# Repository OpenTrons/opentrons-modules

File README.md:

# Opentrons Modules

This repository contains:
1. Firmware for all Opentrons modules - Temperature Module (Tempdeck),
Magnetic Module (Magdeck) and Thermocycler.
2. Libraries required to build any module firmware
3. Module board file definitions for Arduino (for the arduino-based modules)
4. Other files required for development & testing

## setup

This repo uses [CMake](https://cmake.org) as a configuration and build management tool. It requires
CMake 3.20 since it uses [presets](https://cmake.org/cmake/help/latest/manual/cmake-presets.7.html)
to manage cross-compilation and project configuration options. 
- Before you can configure any of the cmake presets, you may need to manually install a C compiler and a C++ compiler (e.g. `sudo apt install gcc g++` on Ubuntu)
- If you want to interact with the STM32 hardware, you should also install [st-link](https://github.com/stlink-org/stlink). 

First, clone the repository and change into the directory:

```
git clone git@github.com:Opentrons/opentrons-modules.git
cd opentrons-modules
```

Then,
- If you want to build the arduino modules, run `cmake --preset=arduino .` to set your build step up to build the Arduino-based modules (Magnetic Module, Temperature Module, Thermocycler). This should download the Arduino IDE to the git-ignored `arduino_ide` directory in the repo's working tree. It will also set up a build system in `./builds`.
- If you want to build the STM32 modules, run `cmake --preset=stm32-cross .` to set your build step up to cross-compile the module firmwares for actually putting on modules. This should download the arm cross builds of gcc 10-2020q4 to the git-ignored `stm32-tools` directory in the repo's working tree and set up a build system in `./build-stm32-cross`. By default, this will be a "MinSizeRel" build type, which generates debug symbols packed into the elf and doesn't use optimizations (which makes debugging a lot easier). You can change the build type by adding `-DCMAKE_BUILD_TYPE=<BUILD_TYPE>` on the command line when generating. Valid build types are `Debug`, `MinSizeRel` (default, size optimizations for release - what CI uses to build), and `RelWithDebInfo` (optimizations + debug info, useful if you're seeing failures in the field that don't happen in `Debug` builds).
  - If you want to enable assertions for debugging, add `-DENABLE_ASSERTIONS=ON` to this command. If you don't specify this option, the `configASSERT` lines in compiled firmware will not do anything.
- If you want to build the STM32 module tests, run `cmake --preset=stm32-host .` to set your build step up to host-compile the module fimrware libs and tests for local running. You'll need to have at least a gcc installed; if you have a clang installed, the build will run some clang checker steps. This will set up a build system in `./build-stm32-host`

Since all these configuration steps use separate build dirs (BINARY_DIRS in cmake parlance) you can in fact run all three of these; it's not exclusive. They should all work on any operating system, but the host builds in particular rely on your system compiler and that will therefore need to be set up, which might be a pain on windows.

## build

Each build dir should have a reasonable `all` target (invokable by running `cmake --build <build-dir>`) and individual targets for each module firmware. For instance, the arduino modules have `<module-name>` set up as individual build targets. 

You always have to specify the build dir to run in with `cmake --build`; that can be run from the root of the repo (e.g. by calling `cmake --build ./build-stm32-cross` or `cmake --build ./build`) or as `.` if you navigate into the right build directory first.

To build a specific target, use the `--target` flag: `cmake --build ./build --target magdeck`.

For the arduino modules, the module name target builds the sketch and copies some supporting files like a python-based uploader and a hex for writing the eeprom into `builds/module-name`. For arduino modules, the special target `zip-all` will build zip files of all module firmwares and support files (e.g. eeprom writing): `cmake --build ./build-arduino --target zip-all`. You can then run `cmake --install ./build` and those zip files will be put in the `dist/` directory; this is used in ci.

For stm32 modules, there are module name targets that build the requisite firmware defined in the cross toolchain and the test toolchain alike. In the cross toolchain, these build runnable firmwares; in the host toolchain, they build everything necessary to run tests, but running the tests is done with `cmake --test`.

## upload

This is not implemented in cmake for the arduino modules. Use the Arduino IDE installed to upload the firmware file:

Open the `/modules/.../<file_name>.ino` file in Arduino, select the appropriate board from _Tools->board_,
 select the correct port from _Tools->Port_. Select Upload or _Sketch->Upload_

* NOTE: For Thermocycler, you can also use the `firmware_uploader.py` script in thermo-cycler/production to upload the binary.

The stm32 modules have debug harnessing built in; for instance, running `cmake --build ./build-stm32-cross --target heater-shaker-debug` will build the firmware and spin up the cross gdb and openocd. This target by default (because of commands in the gdbinit) will reset the board and upload the built firmware; if you want to use the firmware currently flashed to the board, run everything manually.

The stm32 modules also have flash targets for when you want to flash the board but not actually run a debugger; running `cmake --build ./build-stm32-cross --target heater-shaker-flash` will build the firmware and then use openocd to flash it to the target.

## test

This is not implemented for the arduino modules.

For the STM32 modules, if you configure the host toolchain: `cmake --preset=stm32-host .`, you can then run the `build-and-test` target: `cmake --build ./build-stm32-host --target build-and-test`, which will build the tests and then run them. You can also use cmake's built-in `test` target: `cmake --build ./build-stm32-host --target test`, but this will not automatically actually build the tests.

Individual tests may set their own check targets; for instance, you can build and run only the heater-shaker tests by running `cmake --build ./build-stm32-host --target heater-shaker-build-and-test`.

If you are on OSX, you almost certainly want to force cmake to select gcc as the compiler used for building tests, because the version of clang built into osx is weird. We don't really want to always specify the compiler to use in tests, so forcing gcc is a separate cmake config preset, and it requires installing gcc 10:

`brew install gcc@10`
`cmake --preset=stm32-host-gcc10 .`

You should specifically do this if you're seeing errors about `concepts` not existing, or `forward_iterator` not existing, or the like.

You can change to a different compiler, like an installed upstream clang/llvm, by changing the cache variables `CMAKE_C_COMPILER` and `CMAKE_CXX_COMPILER`, or by making a custom configuration (see below) that specifies them.

This isn't the default `stm32-host` because it requires specifying the compiler by version to actually work on OSX, where `gcc` and `g++` unqualified by version are... aliased to system clang. Setting the default to `gcc-10` and `g++-10` then might have problems on other platforms if someone update their gcc and g++ or on CI.

## code coverage

This repository is configured to generate code coverage from the tests.

To enable code coverage, configure the host toolchain for tests with the options `-DENABLE_COVERAGE=On -DCMAKE_BUILD_TYPE=Debug`. _In order for code coverage to be accurate, you must run the build-and-test target for a module_. After running every build-and-test target, the target `lcov` will generate an HTMl report of the code coverage from the tests.

In general, do not enable code coverage unless you need it. Test execution will be far slower.

### Custom Configuration

CMake allows you to set preset overrides through a gitignored file called CMakeUserPresets.json. An example (that implements `stm32-host-gcc`, which is the preset above, as an example) is bundled in the `examples/` folder. To apply it, you would copy it into the root of the repo after checkout. `CMakeUSerPresets.json` works exactly like `CMakePresets.json`, but lets you make system- or IDE-specific configuration. In general, presets in `CMakeUserPresets` should inherit from those in `CMakePresets`, since most of the settings in the checked-in presets are good and only a couple need to be changed, but really it's up to you.

## Contributing

When writing or changing the cmake build system, please follow [modern CMake](https://cliutils.gitlab.io/modern-cmake) practices. Use targets; use generator expressions to set properties on those targets rather than setting ``CMAKE_DEBUG_FLAGS``; write CMake like the programming language it is.

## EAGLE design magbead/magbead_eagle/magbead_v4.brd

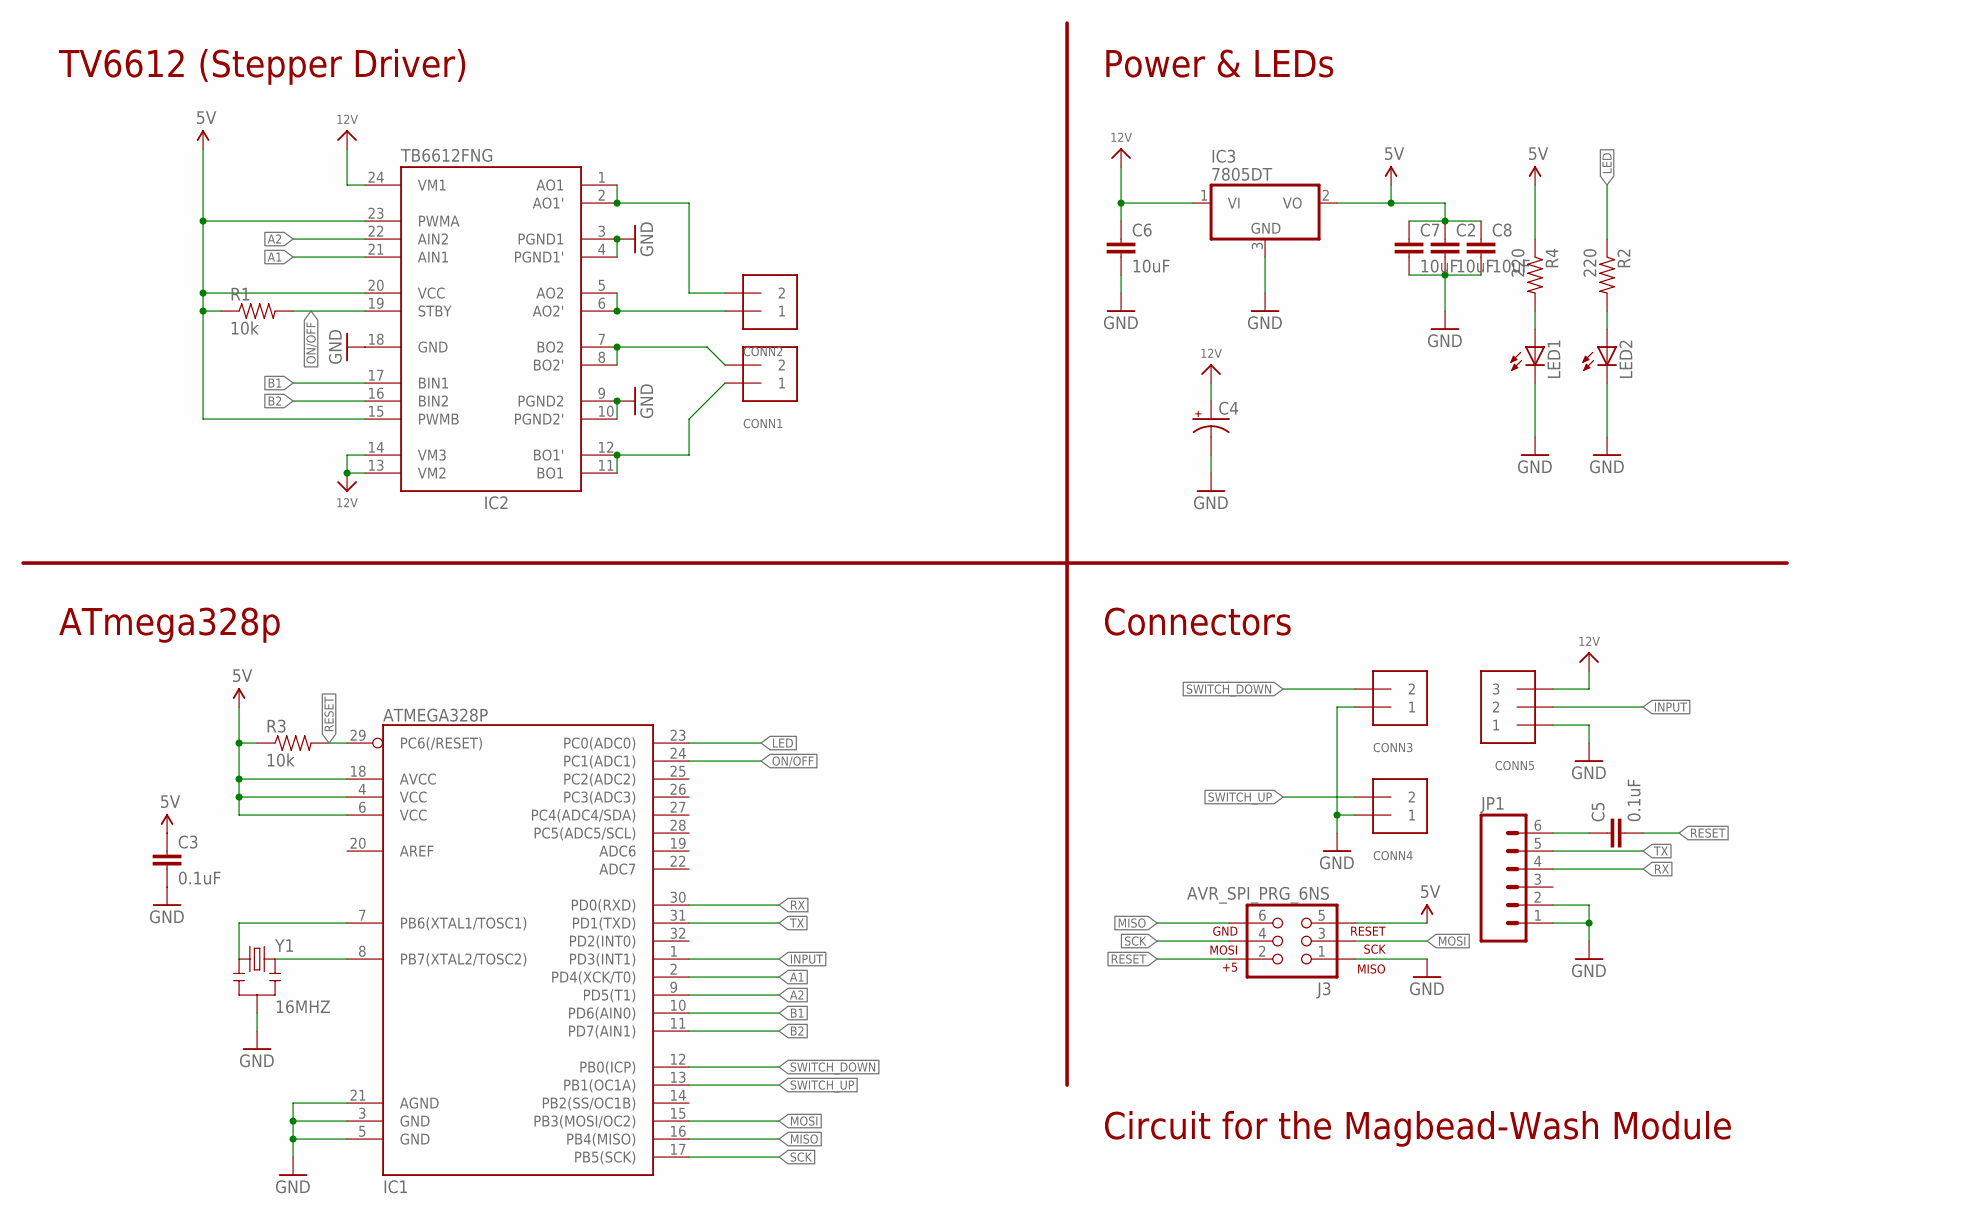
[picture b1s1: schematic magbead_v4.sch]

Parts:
C2, C6, C7, C8: 10uF; 0805
C3, C5: 0.1uF; 0603-CAP
C4: CAP_POLD; PANASONIC_D
CONN1, CONN2, CONN3, CONN4: TERMBLOCK_1X2; TERMBLOCK_1X2-3.5MM
CONN5: TERMBLOCK_1X3; TERMBLOCK_1X3-3.5MM
IC1: ATMEGA328P; TQFP32-08
IC2: TB6612FNG; SSOP24
IC3: 7805DT; TO252
J3: AVR_SPI_PRG_6NS; 2X3-NS
JP1: M06SIP; 1X06
LED1, LED2: LEDCHIP-LED0603; CHIP-LED0603
R1, R3: 10k; 0603-RES
R2, R4: 220; 0603-RES
Y1: 16MHZ; RESONATOR-SMD

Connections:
5V: C2.1, C3.1, C7.1, C8.1, IC1.4 (VCC), IC1.6 (VCC), IC1.18 (AVCC), IC2.15 (PWMB), IC2.20 (VCC), IC2.23 (PWMA), IC3.2 (VO), J3.5, R1.1, R3.1, R4.1
12V: C4.+, C6.1, CONN5.3, IC2.13 (VM2), IC2.14 (VM3), IC2.24 (VM1), IC3.1 (VI)
A1: IC1.2 (PD4(XCK/T0)), IC2.21 (AIN1)
A2: IC1.9 (PD5(T1)), IC2.22 (AIN2)
B1: IC1.10 (PD6(AIN0)), IC2.17 (BIN1)
B2: IC1.11 (PD7(AIN1)), IC2.16 (BIN2)
GND: C2.2, C3.2, C4.-, C6.2, C7.2, C8.2, CONN3.1, CONN4.1, CONN5.1, IC1.3 (GND), IC1.5 (GND), IC1.21 (AGND), IC2.3 (PGND1), IC2.4 (PGND1'), IC2.9 (PGND2), IC2.10 (PGND2'), IC2.18 (GND), IC3.3 (GND), J3.1, JP1.1, JP1.2, LED1.C, LED2.C, Y1.2
INPUT: CONN5.2, IC1.1 (PD3(INT1))
LED: IC1.23 (PC0(ADC0)), R2.1
MISO: IC1.16 (PB4(MISO)), J3.6
MOSI: IC1.15 (PB3(MOSI/OC2)), J3.3
unnamed: LED2.A, R2.2
unnamed: CONN2.2, IC2.1 (AO1), IC2.2 (AO1')
unnamed: LED1.A, R4.2
unnamed: IC1.8 (PB7(XTAL2/TOSC2)), Y1.3
unnamed: IC1.7 (PB6(XTAL1/TOSC1)), Y1.1
unnamed: C5.1, JP1.6
unnamed: CONN2.1, IC2.5 (AO2), IC2.6 (AO2')
unnamed: CONN1.2, IC2.7 (BO2), IC2.8 (BO2')
unnamed: CONN1.1, IC2.11 (BO1), IC2.12 (BO1')
ON/OFF: IC1.24 (PC1(ADC1)), IC2.19 (STBY), R1.2
RESET: C5.2, IC1.29 (PC6(/RESET)), J3.2, R3.2
RX: IC1.30 (PD0(RXD)), JP1.4
SCK: IC1.17 (PB5(SCK)), J3.4
SWITCH_DOWN: CONN3.2, IC1.12 (PB0(ICP))
SWITCH_UP: CONN4.2, IC1.13 (PB1(OC1A))
TX: IC1.31 (PD1(TXD)), JP1.5

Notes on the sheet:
Power & LEDs
Connectors
ATmega328p
TV6612 (Stepper Driver)
Circuit for the Magbead-Wash Module

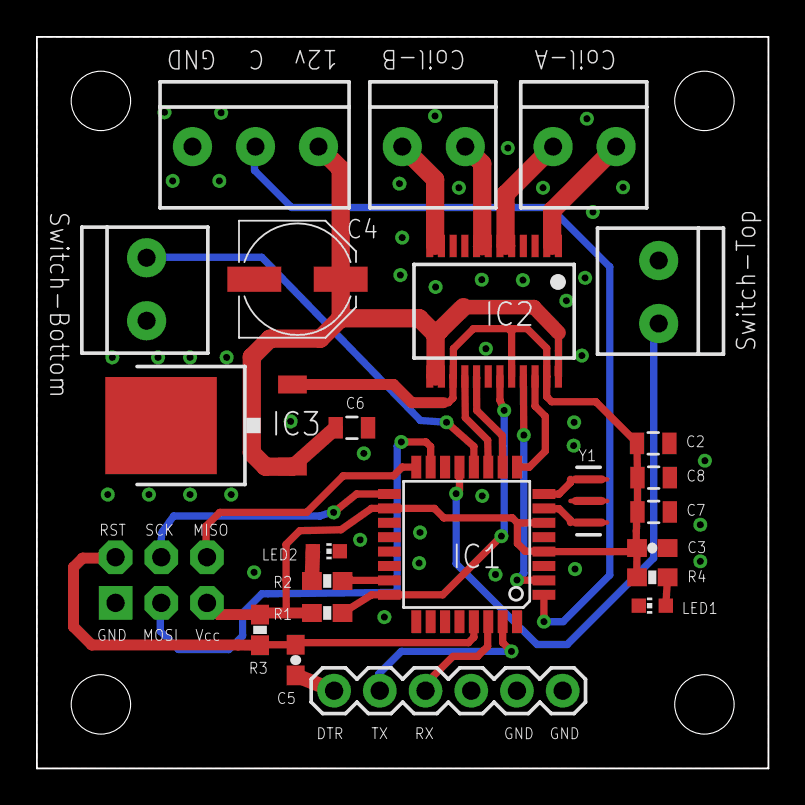
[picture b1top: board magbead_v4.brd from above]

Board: 2 copper layers, 40.6 x 40.6 mm, 24 parts (0 on the bottom side), 27 nets.

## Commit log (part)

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2025-04-03 format
2025-04-04 extra imports
2025-04-14 fix(flex-stacker): ui task fixes and improvements to performance and utility.
2025-04-15 - remove unused freertos timer from motor task - Only enable/disable sensor when there is a state change.
2025-04-23 add task_ready sync status for host comms
2025-04-24 format common
2025-04-24 fix(flex-stacker): Various fixes + improvements for the Flex Stacker UI task and statusbar. (#522)
2025-05-06 always clear cache after error
2025-05-12 fix(thermocycler): clear cache after motor-related errors (#523)
2025-05-12 dont treat error like a flag
2025-05-14 only check limit switch at end of sequence
2025-05-15 update brake delay
2025-05-15 fixup! update default motor currents
2025-05-15 remove semicolon
2025-05-16 remove comment
2025-05-16 fix(flex-stacker): add atomics + remove the UNEXPECTED_LIMIT_SWITCH error from the motor interrupt. (#526)
2025-05-20 test working j gross
2025-05-20 extra whitespace
2025-06-13 Grab reset flags on startup (#485)
2025-06-16 fix print statement
2025-06-16 put default handling in the default case
2025-06-16 gitignore
2025-06-20 cast code to string
2025-06-25 board rev b2 for PVT
2025-08-12 Flex Stacker Release v1.0.0
2025-08-26 fix(flex-stacker): Explicitly enable the limit switch irq on boot to clear any pending irqs held after a fw update.
2025-09-02 add TRAVIS_TAG to get correct arduino module being built
2025-09-02 remove debug
2025-09-15 implement the set_ramp_rate message.
2025-09-15 update tests.
2025-09-16 hetaer-shaker: add test gcodes and basic tests
    Adds M412.D (set error debug), M413 (clear error state), and M411 (get
    error state). These are for checking on and controlling the tracked
    error state of the heater shaker heater and motor tasks for asynchronous
    error generation.
2025-09-16 add clear error state tests
2025-09-16 refactor: clear state motor tests
2025-09-16 fix sim
2025-09-17 reset the leds after power is reset
2025-09-18 refactor: pull some repetitive includes out of tests
2025-09-19 refactor: improve tests
    Take the same approach to the tests as the heater-shaker, condensing
    host comms message checking.
2025-09-19 feat: thermal plate get-error
2025-09-19 feat: add error handling to thermal plate
    The error handling works like this:
    - We will save an "interrupted-by" error that persists until the next
    GetErrorState message, even if the error that caused it originally goes
    away. This is important so that we don't miss transient errors that
    cancelled any ongoing work
    - We get an ongoing error state in preference to an interrupted-by
2025-09-19 Format lots of stuff
2025-09-22 fix: allow messages on subsequent HCT runs
    If the host comms task sends responses too fast it'll clobber the
    previous buffer. Avoid this with a nice little sleep since the stm32 usb
    class doesn't appear to let you see when a buffer has been sent.
2025-09-22 fix lint
    The null pointer thing might be this bug:
    https://bugs.llvm.org/show_bug.cgi?id=46235 the others are just a little
    gross. I might want to disable the constant array index one because if
    you're not going to tolerate exceptions, as we don't, then it's not a
    good idea.
2025-09-24 format said test
2025-09-30 heater-shaker: add a wait after send
    This looks gross and is gross but fixes an issue where if the host comms
    task has two messages to send in quick succession, you can end up
    running again swapping out the tx buffer before it actually hits the wire.
2025-10-01 add usb tx backpressure
    We can actually get whether the usb is busy out of the usb cdc
    machinery. We can use that to handle delaying and retrying if the usb is
    busy, and waiting until the usb transaction completes to actually send data.
2025-10-01 feat(reference-module): add reference module project (#535)
2025-10-03 feat(vacuum-module): add vacuum module project
2025-10-14 fix(thermocycler-gen2): reset lid pos cache if err
    Our fix to EXEC-1451 was to detect if the lid status switches detected
    that we weren't actually closed after the seal extended and return an
    error. This works great. The problem is that because this check happens
    in the lid state machine, the lid _hinge_ state machine has already done
    its work and cached that the lid is closed. Then, when the robot retries
    the command, the lid switches report in-between but we fall back to the
2025-10-15 feat(vacuum-module): add status bar led support.
2025-10-17 feat(vacuum-module): add support for the IS31FL LED driver and status bar animations and controls. (#539)
2025-10-23 use HAL_I2C_Master_Transmit_IT and HAL_I2C_Master_Receive_IT directly and add hal_i2c_master_read and hal_i2c_master_write respective functions fix an issue with the i2c3 buss init
2025-10-23 feat(reference/vacuum-module): Fix gpio issues with i2c3 + add hal_i2c_master_read and hal_i2c_master_write (#540)
2025-10-29 MPR Pressure Sensor hw setup
2025-10-30 temp
2025-10-30 format again
2025-11-03 add vent/pump hardware and policy
2025-11-04 rm stale comments/code
2025-11-04 save
2025-11-05 turn off pump on start
2025-11-06 rm old code + comment
2025-11-06 move sensor hw init
2025-11-06 include hw files in CMakeList
2025-11-06 handle 16-bit timer overflows for accurate tick count
2025-11-07 add pressure control task
2025-11-07 cstdint
2025-11-07 make read buff global variable
2025-11-07 make 0 retries possible
2025-11-07 use write buffer
2025-11-10 - fixed an issue with timing the abs and atm pressure from both sensors - fixed an issue with converting the pressure readings correctly - fixed an issue with the i2c_master_write was being used inst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
2025-11-12 add pressure_task and pump_task skeletons
2025-11-12 remove i2c dep from pump task
2025-11-12 add get pressure engine task
2025-11-13 remove unused vacuum / atmosphere pressure policy use 0x5D instead of 0x5C for atmospheric sensor, since its pull high add sleep_ms to i2c_comms class instantiate abs/atm pressure sensors and get fir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
2025-11-13 add driving mechanism for pressure get and integration
2025-11-13 read abs sensor b, for testing
2025-11-14 fix write + sleep
2025-11-14 rename MPRL to lowercase
2025-11-14 use resume/suspend to start/stop the get pressure task
2025-11-14 add pump control + pid for pump task
2025-11-15 add GetPumpState gcode
2025-11-15 remove unused pressure dirs
2025-11-17 add pressure readings from all 3 pressure sensors
2025-11-18 save pressure/pump controls
2025-11-20 lint
2025-11-25 gets test data through gcode
2025-11-26 formatting
2025-11-26 make read function returns optional
2025-12-01 pump control changes
2025-12-02 unneeded i2c change
2025-12-02 get good gcode readings
2025-12-03 more adjustments for pump task
2025-12-03 pressure regulation achieved
2025-12-04 add is_device_ready to reference-module
2025-12-05 debugging
2025-12-10 save changes for optimizing the pressure task
2025-12-12 after rebase
2025-12-16 - fix timerwrap underflow bug - fix blind start when not enough samples - fix rpm read latensy by decreasing rpm filter alpha
2025-12-16 add EMA pressure filter
2025-12-19 fix issue with atm pressure sensor for nff2 board, which uses ic lps22hb instead of lps22df
2025-12-28 use target guage pressure instead of absolute pressure for user interface
2026-01-05 fix issue parsing negative pressure values
2026-01-07 add comment to explain how the pressure control works
2026-01-07 filter added to new driver version, not used
2026-01-07 filter convolution version
2026-01-08 feat(vacuum-module): Add the pressure and pump control architecture + base gcodes (#544)
2026-01-12 fixed buffer index bug
2026-01-14 clean up comments,test code
2026-01-14 remove filtering from pressure task
2026-01-15 use std arrays
2026-01-15 actual convolution- works
2026-01-15 lint happy + works
2026-01-15 use size_t for buffers + rm sensor_alpha
2026-01-15 comment
2026-01-15 shorter filter
2026-01-20 feat(vacuum-module): set up FIR filtering for vacuum pressure sensor readings (#547)
2026-01-27 separate sensor read set up, still has compile errors
2026-02-11 call send pressure state from GPIO it
2026-02-18 feat(vacuum-module): add product id for vacuum module.
2026-02-19 feat(vacuum-module): add gcodes to tune the pressure control PID parameters.
2026-02-19 fix(build): add vacuum-module to set_build_vars script to deploy the firmware to aws.
2026-02-24 fix(vacuum-module): convert unweighted filter to EMI when filtering mprll0025pa00001a pressure readings.
2026-02-26 get command issues timestamp
2026-02-26 return after stop vacuum + rm dummy function from atm sensor driver
2026-02-26 add solid state tracking + duration
2026-03-02 software timer working
2026-03-05 vent after working
2026-03-05 rm some old comments
2026-03-06 use send_error_message + rename sstp
2026-03-06 feat(vacuum-module): add a slope monitoring mechanism for waste full detection.
2026-03-06 change SetVentState to use VentState enum instead of bool
2026-03-09 feat(vacuum-module): Expose temperature in Celcius from the lps22hb pressure sensor.
2026-03-11 split out pressure control and waste detection into seperat classes
2026-03-17 feat(vacuum-module): Add a waste full detection mechanism using pressure slope monitoring (#555)
2026-03-18 feat(vacuum-module): add SetWasteConfig and GetWasteConfig gcodes. (#557)
2026-03-19 fix(vacuum-module): fix SetWasteConfig gcode respose.
2026-03-19 fix(vacuum-module): fix SetWasteConfig gcode respose. (#558)
2026-03-24 feat(vacuum-module): Add pressure not reached configuration.
2026-03-27 fix: correct reset reason logic
    The reset reason logic had a couple issues
    - Not all the RCC flags are about reset reasons; some of them are more
    in the CC than the R (of Reset and Clock Control) and are about
    monitoring the readiness of internal clock sources. Omit these
    - The logic would only emit the first positive flag it found, which in
    the current implementation was always one of the clock readiness flags.
2026-03-27 fix(vacuum-module): fix init issue with lps22hb resulting in bad pressure values. (#561)
2026-04-29 fix(vacuum-module): Increase the max pwm of the vacuum module to 100
2026-05-18 feat(vacuum-module): add vacuum duration to GetPressureState.
2026-05-19 feat(vacuum-module): add standard deviation to waste detection + volumetric flow rate calculation.
2026-05-19 feat(vacuum-module): add DAC support for controlling the solenoid valve current. (#564)
2026-05-21 Force the heater_hardware_power_set function into a critical section when called from a task, additionally we can make the heater_started variable volitale to be more explicit in code but disassembly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
2026-05-22 fix unit tests
2026-05-28 feat(vacuum-module): add standard deviation to waste detection + volumetric flow rate calculation. (#565)
2026-06-01 fix(vacuum-module): set correct 8-bit DAC range of 256 instead of 4096 when setting the vent voltage. (#567)
2026-06-04 feat(vacuum-module): add notify mechanism to the pump_task so we can use duration + waste detection logic of the pressure task. (#568)
2026-06-08 fix(heater-shaker): fix PWM deadlock
2026-06-15 fix(vacuum-module): fix issue with direct duty cycle control not going through ramp logic
2026-06-16 fix(vacuum-module): Fixes some issues with the SetPumpState message logic and acks. (#570)
2026-06-17 fix(vacuum-module): fixes an issue with NotifyPumpRunMessage not working correctly for SetPumpMessage. (#571)

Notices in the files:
parts and their libraries:
microbuilder: This work is placed in the public domain, and may be freely used for commercial and non-commercial work with the following conditions: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
SparkFun-DigitalIC: Licensing: Creative Commons ShareAlike 4.0 International - https://creativecommons.org/licenses/by-sa/4.0
